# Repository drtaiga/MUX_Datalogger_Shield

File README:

This repository contains all of the information required to produce 
multiplexer-datalogger shield for the Arduino Uno. The shield features two
sets of heavy duty screw terminals for coupling sensors to the Arduino.
It is assumed that each sensor has three leads: one for power (3.3V), one for
a ground connection, and one for a return signal (0-3.3V). The shield also
has a 4051 8x1 multiplexer for switching between the eight analog inputs, and
it accomodates an SD card for data storage.

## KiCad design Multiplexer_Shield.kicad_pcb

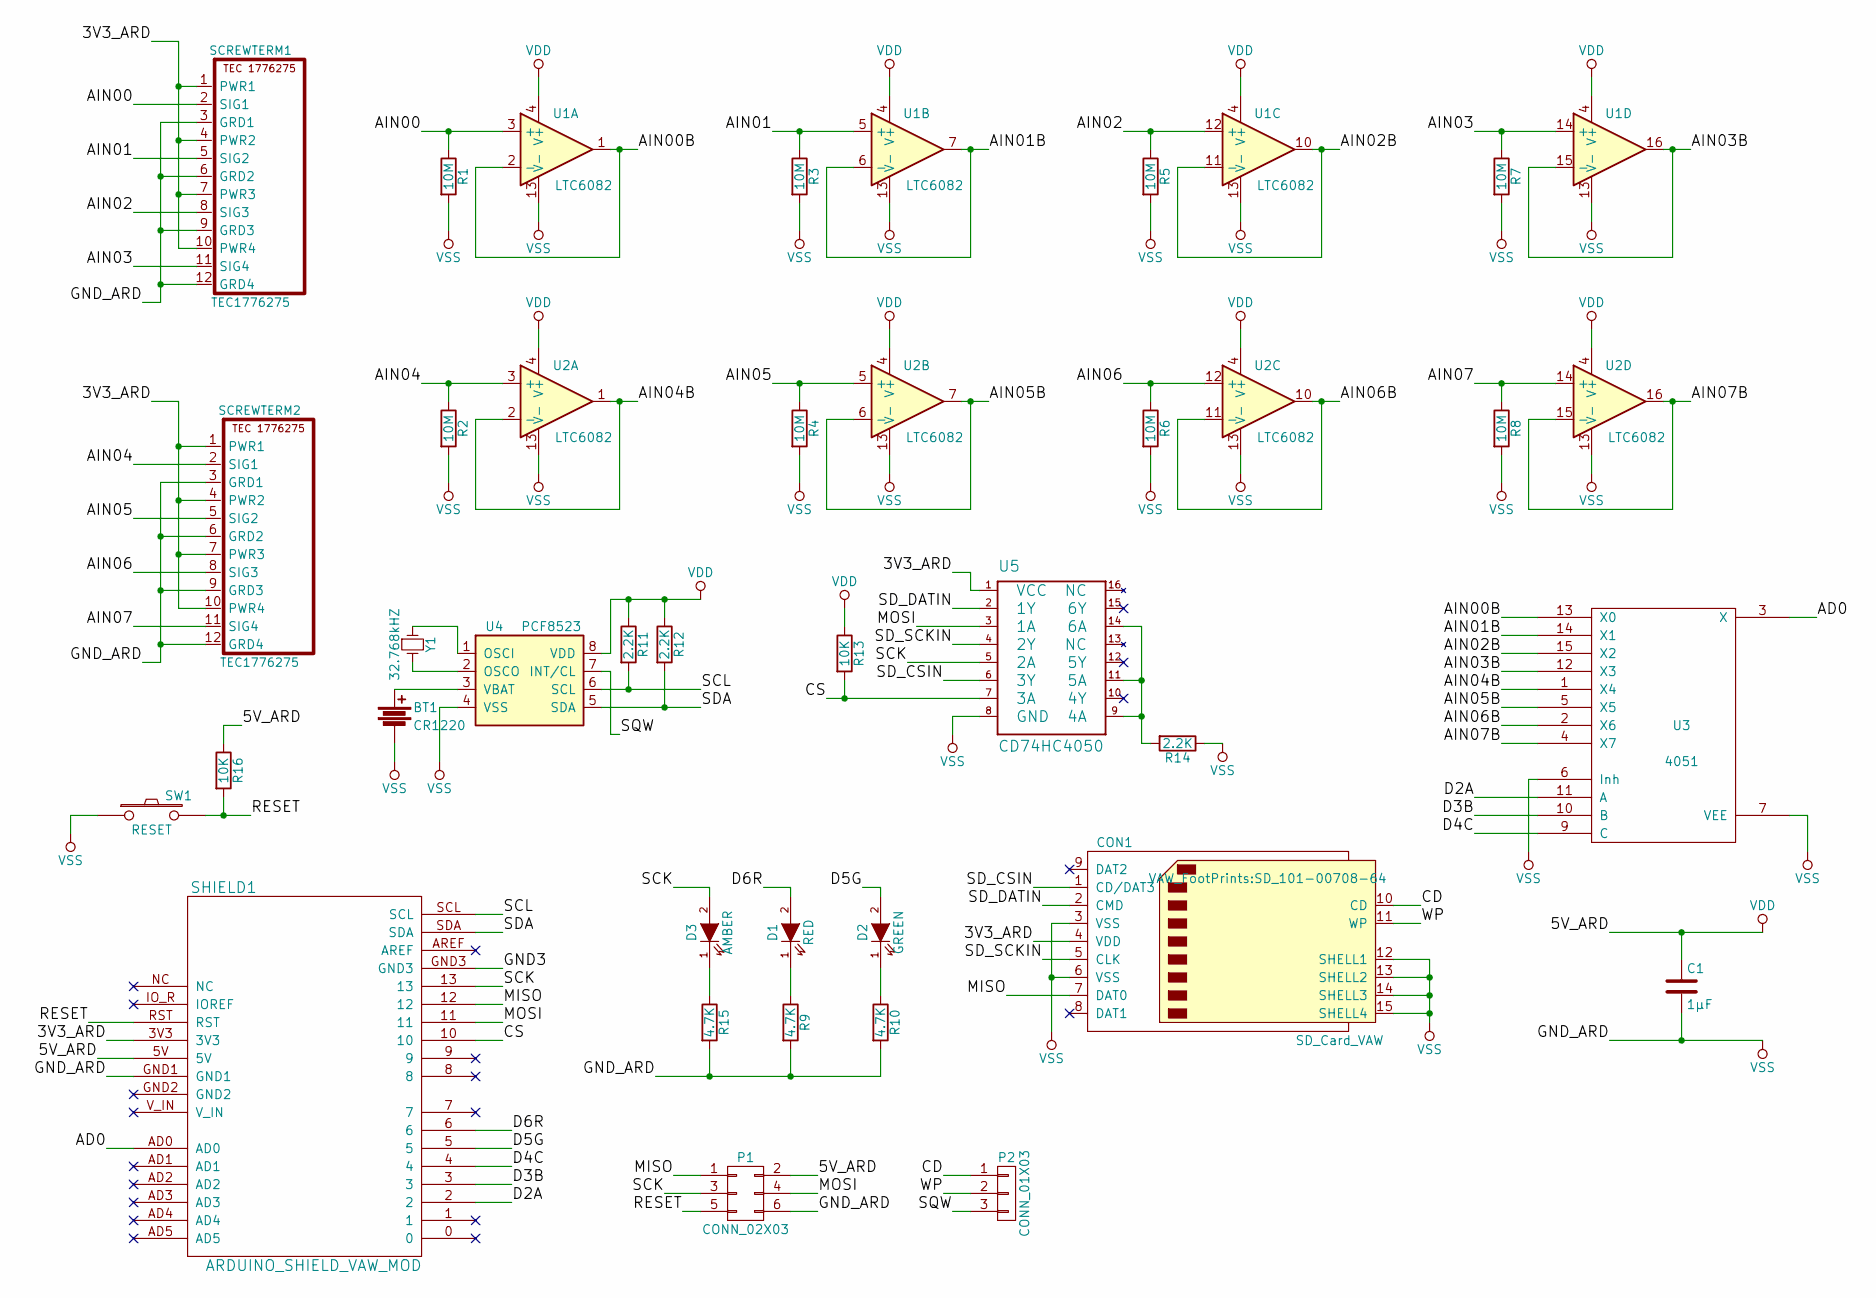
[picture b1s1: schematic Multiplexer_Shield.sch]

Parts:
BT1: CR1220; keystone_500
C1: 1µF; CAP_TANT_3216
CON1: SD_Card_VAW; SD_101-00708-64
D1: RED; LED_1206
D2: GREEN; LED_1206
D3: AMBER; LED_1206
P1: CONN_02X03; Pin_Header_Straight_2x03
P2: CONN_01X03; Pin_Header_Straight_1x03
R1, R2, R3, R4, R5, R6, R7, R8: 10M; R_1206_HandSoldering
R9, R10, R15: 4.7K; R_1206_HandSoldering
R11, R12, R14: 2.2K; R_1206_HandSoldering
R13, R16: 10K; R_1206_HandSoldering
SCREWTERM1, SCREWTERM2: TEC1776275; TerminalBlock_Pheonix_PT-3.5mm_12pol
SHIELD1: ARDUINO_SHIELD_VAW_MOD; ARDUINO_SHIELD_VAW_3
SW1: RESET; PCB_PUSH
U1, U2: LTC6082; SO-16-N
U3: 4051; SO-16-N
U4: PCF8523; SOIC-8-N
U5: CD74HC4050; SO-16-N
Y1: 32.768kHZ; R_0805_HandSoldering

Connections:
/3V3_ARD: CON1.4 (VDD), SCREWTERM1.1 (PWR1), SCREWTERM1.4 (PWR2), SCREWTERM1.7 (PWR3), SCREWTERM1.10 (PWR4), SCREWTERM2.1 (PWR1), SCREWTERM2.4 (PWR2), SCREWTERM2.7 (PWR3), SCREWTERM2.10 (PWR4), SHIELD1.3V3, U5.1 (VCC)
/AD0: SHIELD1.AD0, U3.3 (X)
/AIN00: R1.1, SCREWTERM1.2 (SIG1), U1.3 (+)
/AIN00B: U1.1, U1.2 (-), U3.13 (X0)
/AIN01: R3.1, SCREWTERM1.5 (SIG2), U1.5 (+)
/AIN01B: U1.6 (-), U1.7, U3.14 (X1)
/AIN02: R5.1, SCREWTERM1.8 (SIG3), U1.12 (+)
/AIN02B: U1.10, U1.11 (-), U3.15 (X2)
/AIN03: R7.1, SCREWTERM1.11 (SIG4), U1.14 (+)
/AIN03B: U1.15 (-), U1.16, U3.12 (X3)
/AIN04: R2.1, SCREWTERM2.2 (SIG1), U2.3 (+)
/AIN04B: U2.1, U2.2 (-), U3.1 (X4)
/AIN05: R4.1, SCREWTERM2.5 (SIG2), U2.5 (+)
/AIN05B: U2.6 (-), U2.7, U3.5 (X5)
/AIN06: R6.1, SCREWTERM2.8 (SIG3), U2.12 (+)
/AIN06B: U2.10, U2.11 (-), U3.2 (X6)
/AIN07: R8.1, SCREWTERM2.11 (SIG4), U2.14 (+)
/AIN07B: U2.15 (-), U2.16, U3.4 (X7)
/CD: CON1.10 (CD), P2.1
/CS: R13.2, SHIELD1.10, U5.7 (3A)
/D2A: SHIELD1.2, U3.11 (A)
/D3B: SHIELD1.3, U3.10 (B)
/D4C: SHIELD1.4, U3.9 (C)
/D5G: D2.2 (A), SHIELD1.5
/D6R: D1.2 (A), SHIELD1.6
/MISO: CON1.7 (DAT0), P1.1, SHIELD1.12
/MOSI: P1.4, SHIELD1.11, U5.3 (1A)
/RESET: P1.5, R16.2, SHIELD1.RST, SW1.2
/SCK: D3.2 (A), P1.3, SHIELD1.13, U5.5 (2A)
/SCL: R11.2, SHIELD1.SCL, U4.6 (SCL)
/SDA: R12.2, SHIELD1.SDA, U4.5 (SDA)
/SD_CSIN: CON1.1 (CD/DAT3), U5.6 (3Y)
/SD_DATIN: CON1.2 (CMD), U5.2 (1Y)
/SD_SCKIN: CON1.5 (CLK), U5.4 (2Y)
/SQW: P2.3, U4.7 (INT/CL)
/WP: CON1.11 (WP), P2.2
unnamed: BT1.1, U4.3 (VBAT)
unnamed: D1.1 (K), R9.1
unnamed: D2.1 (K), R10.1
unnamed: D3.1 (K), R15.1
unnamed: R14.2, U5.9 (4A), U5.11 (5A), U5.14 (6A)
unnamed: U4.1 (OSCI), Y1.1
unnamed: U4.2 (OSCO), Y1.2
VDD: C1.1, P1.2, R11.1, R12.1, R13.1, R16.1, SHIELD1.5V, U1.4 (V+), U2.4 (V+), U3.16 (VDD), U4.8 (VDD)
VSS: BT1.2, C1.2, CON1.3 (VSS), CON1.6 (VSS), CON1.12 (SHELL1), CON1.13 (SHELL2), CON1.14 (SHELL3), CON1.15 (SHELL4), P1.6, R1.2, R2.2, R3.2, R4.2, R5.2, R6.2, R7.2, R8.2, R9.2, R10.2, R14.1, R15.2, SCREWTERM1.3 (GRD1), SCREWTERM1.6 (GRD2), SCREWTERM1.9 (GRD3), SCREWTERM1.12 (GRD4), SCREWTERM2.3 (GRD1), SCREWTERM2.6 (GRD2), SCREWTERM2.9 (GRD3), SCREWTERM2.12 (GRD4), SHIELD1.GND1, SW1.1, U1.13 (V-), U2.13 (V-), U3.6 (Inh), U3.7 (VEE), U3.8 (VSS), U4.4 (VSS), U5.8 (GND)

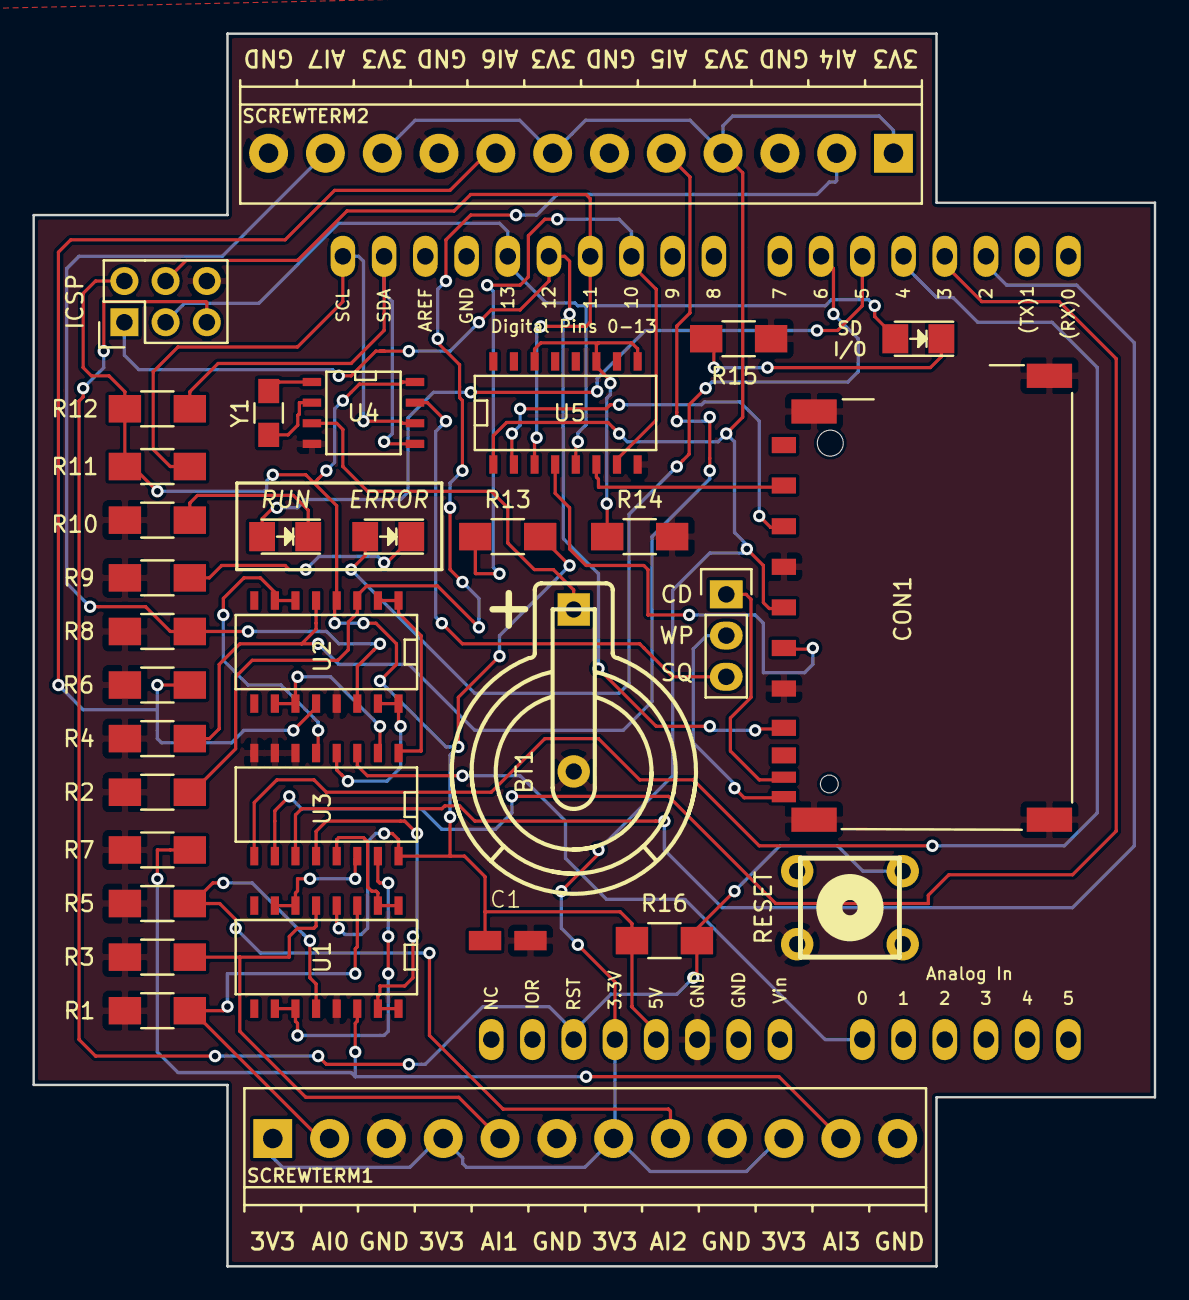
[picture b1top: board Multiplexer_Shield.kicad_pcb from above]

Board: 2 copper layers, 69.1 x 75.9 mm, 34 parts (0 on the bottom side), 45 nets.

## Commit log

2017-01-04 First commit.
2017-01-05 README edit.
